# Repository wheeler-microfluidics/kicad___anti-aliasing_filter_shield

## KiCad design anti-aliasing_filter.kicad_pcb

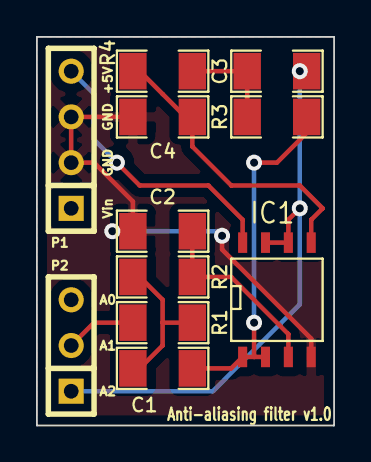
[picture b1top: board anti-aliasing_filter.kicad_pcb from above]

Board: 2 copper layers, 16.5 x 21.6 mm, 11 parts (0 on the bottom side), 9 nets.

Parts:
C1: 0.0047uF; SM1206
C2, C4: 220pF; SM1206
C3: 390pF; SM1206
IC1: MCP6022; SO8N
P1: CONN_4; SIL-4
P2: CONN_3; SIL-3
R1: 1.78k; SM1206
R2: 4.02k; SM1206
R3: 9.09k; SM1206
R4: 20k; SM1206

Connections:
+5V: IC1.8, P1.4
GND: C2.2, C4.2, IC1.4, P1.2, P1.3
unnamed: C4.1, IC1.5, R4.2
unnamed: C1.1, R1.2, R2.1
unnamed: C2.1, IC1.3, R2.2
unnamed: C3.1, R3.2, R4.1
unnamed: C3.2, IC1.6, IC1.7, P2.1
unnamed: P2.2, R1.1
unnamed: C1.2, IC1.1, IC1.2, R3.1

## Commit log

2015-01-26 Change R/C values to make 50kHz LP Chebychev
2015-01-26 Add BOM
2015-02-11 Add *.pos files
2015-02-11 Rename `gerbers` directory `gerber`
2015-02-11 Make drill file compatible with gerbmerge
2015-02-11 Add paste files
2016-01-20 Update .gitmodules file to point to github
2017-07-13 added appveyor.yml
2017-07-14 AppVeyor Configuration Updated
2017-07-15 AppVeyor Update: "5f61b891681557a9814440e47f9102b18ddcac59"
2017-07-17 AppVeyor Update: "ebd3acae5fa1c3216efbc6cb908b5db07f7b5100"
2017-07-17 AppVeyor Update: "f9cc8f1957b59965408d0c40c51fe03863cbf7a2"
2017-07-17 AppVeyor Update: "5d17439f61475bc23d95e0b42b680d8fb34545a9"
2017-07-18 AppVeyor Update: "ed2efe62bb2ab97aa8e77d59d2fbf27f7906765d"
2017-07-18 AppVeyor Update: "a4e909ac7a44d2708564d46a9b978b95c8367686"
2017-07-19 AppVeyor Update: "d5d159050eac48ab9123f383fe8e949476d7f60f"
2017-07-20 AppVeyor Update: "35852f667457a927c170bb71278740b12d7a8f75"
